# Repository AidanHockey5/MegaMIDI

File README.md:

# Mega MIDI

https://www.aidanlawrence.com/mega-midi-a-playable-version-of-my-hardware-sega-genesis-synth/

[Instruction Manual](https://www.aidanlawrence.com/wp-content/uploads/2019/07/MegaMidi5Manual.pdf)

[Store Link](https://www.aidanlawrence.com/product/mega-midi-5/)

This project contains the source material for the Mega MIDI, a MIDI-controlled Sega Genesis/Megadrive Synthesizer that uses the genuine sound chips from the console itself. The primary FM sound source is the Yamaha YM2612, but I have also included the SN76489 PSG which was also present on the Sega Genesis. This synthesizer does not use emulated sound - it's the real deal. Therefore, you are limited to the limitations of the actual hardware, which I will explain in more detail down below.

# Why Not Just Emulate?
You'd be hard-pressed to find an emulated YM2612 core that sounds exactly like the real YM2612. There are some that get close, but nothing compares to the real thing. Yamaha's FM synthesis is pretty tricky to emulate in the first place, but the YM2612's signature gritty DAC is mostly to blame for the lack of truly accurate emulation. Not with The Mega MIDI though. Since you are using the real YM2612 and SN76489 ICs, you can experience playing the Sega Genesis as a musical instrument with the true fidelity and accuracy as the real thing.

# Play Any Instrument from Any Genesis Video Game Music
The Mega MIDI reads in ".opm" files. OPM files were originally designed for the VOPM virtual synthesizer. The OPM format stores the register data for FM patches that you can use to easily program your YM2612 with. FM synthesis is very complicated, so while you still have the option to create your own FM patches, it would be way easier to just directly take the FM voice patches from the games themselves and use them on your Mega MIDI. With the Mega MIDI, you can, in fact, DIRECTLY play FM patches from any Sega Genesis game's music. These aren't "sound-alike" patches either, they are the actual identical patches lifted directly from the game's source. Do you like ThunderForce's Guitar patch in the track Metal Squad? Play it. Want to try your hand playing Chemical Plant Zone's bass patch? Go for it. Any track. Any instrument. Instantly.

# Where Do I find OPM files?
There are two ways:

1) There is a massive pack of ripped OPM files ready to go that spans almost the entire Genesis library. You can find just about anything in this collection. [Click here to download it.](https://www.aidanlawrence.com/wp-content/uploads/2019/03/2612org-OPMs.zip)
One thing to note: This is a REALLY big collection of files. I don't recommend putting them ALL on your SD card at once as load times will begin to suffer. 

2) You can convert any OPN2(YM2612) .VGM file to an OPM patch using the vgm2opm tool courtesy of [Shiru](https://shiru.untergrund.net) and https://github.com/vampirefrog/fmtools

I have included a windows-compiled binary of vgm2opm within the [tools](https://github.com/AidanHockey5/MegaMIDI/tree/master/tools) directory of this repository along with a batch-file to automatically execute the tool. To use this tool, simply place your desired .vgm/vgz files within the VGM_IN folder, double-click the CONVERT_VGM_OPM.bat file, then retrieve your OPM patch files in the OPM_OUT folder.

# USB MIDI and Traditional DIN MIDI Compatible
Want to control The Mega MIDI through software like Ableton, FL Studio, or any other DAW? You can! The Mega MIDI will show up like any other MIDI-compatible instrument and is able to receive native USB MIDI commands without any sort of serial bridge. 
Prefer old-school traditional 5-pin DIN MIDI instead? Go for it! Bust out that classic MIDI controller and plug it in with zero additional setup required.

# Crystal-Clear Amplification 
Now featuring a modified version of the Mega Amp Mod! Beautifully clear amplification for both the YM3438 and the YM2612!

# 7 "Favorite" Buttons to Quickly Swap Between Your Favorite Patches
While you do have access to every .opm file on your Mega MIDI's SD card, sometimes you'll find the *perfect* patch that you'll want to keep for easy-access later. Simply hold-down one of the seven "favorite" buttons at the bottom of the board and your currently loaded patch will be saved into EEPROM. Because favorite patches are saved to EEPROM, you can access them instantaneously without any load times. Perfect for swapping patches on-the-fly!

# Real Hardware, Real Limitations
Because you are working with the real sound chips, you are also working under their real limitations. The YM2612 is a six-channel sound chip, meaning you can play six individual notes at once. The SN76489 PSG is a 3-channel square-wave-only (excluding noise) chip. In total, you can have nine total channels of sound if you're playing both the PSG and the YM2612 at the same time.

While some might find this a bit limiting, others may enjoy the challenge of getting as much sound as they possibly can within the limits of the genuine hardware. Countless other video game music composers did it, now you can experience it too!

# Open-source
All of my source material has been made open-source. Want to build your own Mega MIDI from scratch? Go for it! Have some modifications in mind? I'd love to see them! If you do decide your own version, please credit me: Aidan Lawrence and refer back to this original repository. Please do not resell this project.

# Tools
The firmware for this project was developed in [Visual Studio Code](https://code.visualstudio.com/) with the [PlatformIO extention.](https://docs.platformio.org/en/latest/ide/vscode.html) I used the Teensyduino (ArduinoTeensy) toolchain.

The schematics/PCB files were made with [KiCAD.](http://kicad.org/) Specifically, version 5.0.2.

Precompiled firmware HEX files can be found here:
https://github.com/AidanHockey5/MegaMIDI/releases/

Here is the schematic:

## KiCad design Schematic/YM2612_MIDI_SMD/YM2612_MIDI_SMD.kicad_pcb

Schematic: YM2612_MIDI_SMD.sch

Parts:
C1, C2, C3, C7, C8, C10, C11, C12, C14, C26, C27, C28: 100nF; C_0805
C4, C5: 22pF; C_0603
C6, C20, C21: 1uF; C_0805
C9, C15, C16, C17, C19, C22, C23, C31, C32, C33: 10uF; C_1206
C13: 220pF; C_0603
C18, C29, C30: 100uF; CP_Elec_6.3x7.7
C24, C25: 270pF; C_0805
D1: 1N4148; D_SOD-123
D2: SS34; D_SMA
D4, D5, D6, D7, D8, D9, D10, D11: LED_Small; LED_0805
DS1: LCD20x04; LCD-20x4
H1, H2, H3, H4, H5: MountingHole; MountingHole_3.2mm_M3
J1: DIN-5_180; din-5
J2: TP_GND; Pin_Header_Straight_1x01_Pitch2.54mm
J3: USB_B
J5: ICSP; Pin_Header_Straight_2x03_Pitch2.54mm
J6: Audio-Jack-3; SWITCHCRAFT_35RAPC4BHN2
J7: Micro_SD_Card; SOFNG_TF_15x15_PUSH_PUSH
L1: 10uH; L_4x4
MP1: GRAPHIC; logo_1
MP2: GRAPHIC; logo_2
MP3: GRAPHIC; logo_3
R1: 10k; R_0805
R2, R6, R10, R11, R12, R13, R14, R15, R16, R17: 220; R_0805
R3: 1k; R_0805
R4, R5: 22; R_0805
R7: 270; R_0805
R8, R30: 51K; R_0805
R9: 2.2k; R_0805
R18, R19: 10K; R_0805
R20, R22: 2.2K; R_0805
R21: 1.3K; R_0805
R23, R26: 6.2K; R_0805
R24, R25: 150K; R_0805
R27, R28: 160K; R_0805
R29: 12K; R_0805
RV1: R_POT; 3362P-1-103LF
SW1: Rotary_Encoder_Switch; RotaryEncoder_Alps_EC11E-Switch_Vertical_H20mm
SW2, SW3, SW4, SW5, SW6, SW7, SW8, SW9, SW10: SW_Push_Dual; SW_TH_Tactile_Omron_B3F-10xx
U1: H11L1; SMDIP-6_W7.62mm
U2: AT90USB1286-AU; TQFP-64_14x14mm_Pitch0.8mm
U3: YM2612; DIP-24_W15.24mm
U4: SN76489; DIP-16_W7.62mm
U5: LM2733XMF; SOT-23-5
U6: LD1117S33TR_SOT223; SOT-223-3_TabPin2
U7: 4050; SOIC-16_3.9x9.9mm_Pitch1.27mm
U8: TL072; SOIC-8_3.9x4.9mm_Pitch1.27mm
U9, U10: LD1117S50TR_SOT223; SOT-223-3_TabPin2
Y1: 16MHz; Crystal_SMD_HC49-SD

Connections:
+2V5: C18.1, R18.2, R19.1, U8.3, U8.5
+3V3: C17.1, C26.1, C28.1, J7.4, U6.2, U7.1
+5V: C1.1, C2.1, C3.1, C7.1, C12.2, C32.2, DS1.2, J5.2, R1.1, R6.1, R7.1, R9.1, RV1.1, U1.6, U2.3 (UVCC), U2.8 (VBUS), U2.21 (VCC), U2.52 (VCC), U2.62 (AREF), U2.64 (AVCC), U3.23 (Vcc), U10.2
+5VA: C11.1, C14.2, C27.1, C31.2, R18.1, U3.22 (AVcc), U4.16 (Vcc), U8.8, U9.2
B1: SW2.1, U2.51 (PA0)
B2: SW4.1, U2.50 (PA1)
B3: SW6.1, U2.49 (PA2)
B4: SW9.1, U2.48 (PA3)
B5: SW3.1, U2.47 (PA4)
B6: SW5.1, U2.46 (PA5)
B7: SW7.1, U2.45 (PA6)
B8: SW10.1, U2.44 (PA7)
D0: DS1.7, U2.61 (PF0), U3.2 (D0), U4.10 (D0)
D1: DS1.8, U2.60 (PF1), U3.3 (D1), U4.11 (D1)
D2: DS1.9, U2.59 (PF2), U3.4 (D2), U4.12 (D2)
D3: DS1.10, U2.58 (PF3), U3.5 (D3), U4.13 (D3)
D4: DS1.11, U2.57 (PF4), U3.6 (D4), U4.15 (D4)
D5: DS1.12, U2.56 (PF5), U3.7 (D5), U4.1 (D5)
D6: DS1.13, U2.55 (PF6), U3.8 (D6), U4.2 (D6)
D7: DS1.14, U2.54 (PF7), U3.9 (D7), U4.3 (D7)
GND: C1.2, C2.2, C3.2, C4.2, C5.2, C6.2, C7.2, C8.2, C9.2, C11.2, C12.1, C14.1, C15.1, C16.1, C17.2, C18.2, C23.1, C26.2, C27.2, C28.2, C31.1, C32.1, C33.2, DS1.1, DS1.5, DS1.16, J3.4, J5.6, J6.3, J7.6, J7.9, R3.2, R10.2, R11.2, R12.2, R13.2, R14.2, R15.2, R16.2, R17.2, R19.2, R20.2, R21.2, R22.2, R29.1, RV1.3, SW1.C, SW1.S2, SW2.4, SW3.4, SW4.4, SW5.4, SW6.4, SW7.4, SW8.4, SW9.4, SW10.4, U1.5, U2.6 (UGND), U2.22 (GND), U2.53 (GND), U2.63 (GND), U3.1 (GND), U3.12 (GND), U3.19 (AGND), U4.6 (OE), U4.8 (GND), U5.2, U6.1, U7.8, U7.9, U7.11, U7.14, U8.4, U9.1, U10.1; also elsewhere on the board
LCD_E: DS1.6, U2.16 (PB6)
LCD_RS: DS1.4, U2.42 (PC7)
LED_1: D4.2, U2.26 (PD1)
LED_2: D5.2, U2.28 (PD3)
LED_3: D6.2, U2.29 (PD4)
LED_4: D7.2, U2.30 (PD5)
LED_5: D8.2, U2.31 (PD6)
LED_6: D9.2, U2.32 (PD7)
LED_7: D10.2, U2.14 (PB4)
LED_8: D11.2, U2.17 (PB7)
L_OUT: C29.2, J6.1
MIDI_IN: R7.2, U1.4, U2.27 (PD2)
MISO: J5.1, J7.7, U2.13 (PB3)
MOL: C19.2, R20.1, U3.21 (MOL)
MOR: C22.2, R22.1, U3.20 (MOR)
MOSI: J5.4, U2.12 (PB2), U7.5
unnamed: C4.1, U2.24 (XTAL1), Y1.2
unnamed: C5.1, U2.23 (XTAL2), Y1.1
unnamed: C6.1, U2.7 (UCAP)
unnamed: C10.2, U3.24 (CLOCK_IN)
unnamed: C13.2, R29.2, R30.2, U5.3
unnamed: C19.1, R23.2
unnamed: C20.1, R24.2
unnamed: C21.1, R25.2
unnamed: C22.1, R26.2
unnamed: C24.1, C29.1, R27.1, U8.1
unnamed: C24.2, R23.1, R24.1, R27.2, U8.2
unnamed: C25.1, C30.1, R28.1, U8.7
unnamed: C25.2, R25.1, R26.1, R28.2, U8.6
unnamed: D1.1, R2.1, U1.1
unnamed: D1.2, J1.5, U1.2
unnamed: D2.2, L1.1, U5.1
unnamed: D4.1, R10.1
unnamed: D5.1, R11.1
unnamed: D6.1, R12.1
unnamed: D7.1, R13.1
unnamed: D8.1, R14.1
unnamed: D9.1, R15.1
unnamed: D10.1, R16.1
unnamed: D11.1, R17.1
unnamed: DS1.3, RV1.2
unnamed: DS1.15, R6.2
unnamed: J1.4, R2.2
unnamed: J7.2, U7.2
unnamed: J7.3, U7.4
unnamed: J7.5, U7.6
unnamed: R3.1, U2.43 (PE2/~HWB)
unnamed: R4.1, U2.5 (D+)
unnamed: R5.1, U2.4 (D-)
unnamed: R8.2, U5.4
PSG_CLOCK: U2.41 (PC6), U4.14 (CLOCK_IN)
PSG_OUT: C20.2, C21.2, R21.1, U4.7 (SN_OUT)
PSG_RDY: R9.2, U2.19 (PE5), U4.4 (READY)
PSG_WE: U2.18 (PE4), U4.5 (WE)
RESET: J5.5, R1.2, SW8.1, U2.20 (~RESET)
RE_A: SW1.A, U2.1 (PE6)
RE_B: SW1.B, U2.2 (PE7)
RE_SW: C8.1, SW1.S1, U2.25 (PD0)
R_OUT: C30.2, J6.2
SCK: J5.3, U2.11 (PB1), U7.7
SD_CS: U2.10 (PB0), U7.3
USB_D+: J3.3, R4.2
USB_D-: J3.2, R5.2
VBOOST: C13.1, C15.2, C16.2, C23.2, C33.1, D2.1, R30.1, U6.3, U9.3, U10.3; also elsewhere on the board
VBUS: C9.1, J3.1, L1.2, R8.1, U5.5
YM_A0: U2.39 (PC4), U3.17 (A0)
YM_A1: U2.40 (PC5), U3.18 (A1)
YM_CLOCK: C10.1, U2.15 (PB5)
YM_CS: U2.36 (PC1), U3.14 (CS)
YM_IC: U2.35 (PC0), U3.11 (IC)
YM_RD: U2.38 (PC3), U3.16 (RD)
YM_WR: U2.37 (PC2), U3.15 (WR)

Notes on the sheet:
YM2612 MIDI Synth SMD Version
Tuesday, Feburary 5, 2019
Designed and Programmed by: Aidan Lawrence www.aidanlawrence.com
MCU
Sound Chips
Mixing, Pre-amp & Power Amp
SD Card & Level Translator
Power Delivery
I/O
LCD
MIDI-In
YM3438 Remove: R20 R22
YM3438 Change: R23, R26 51K

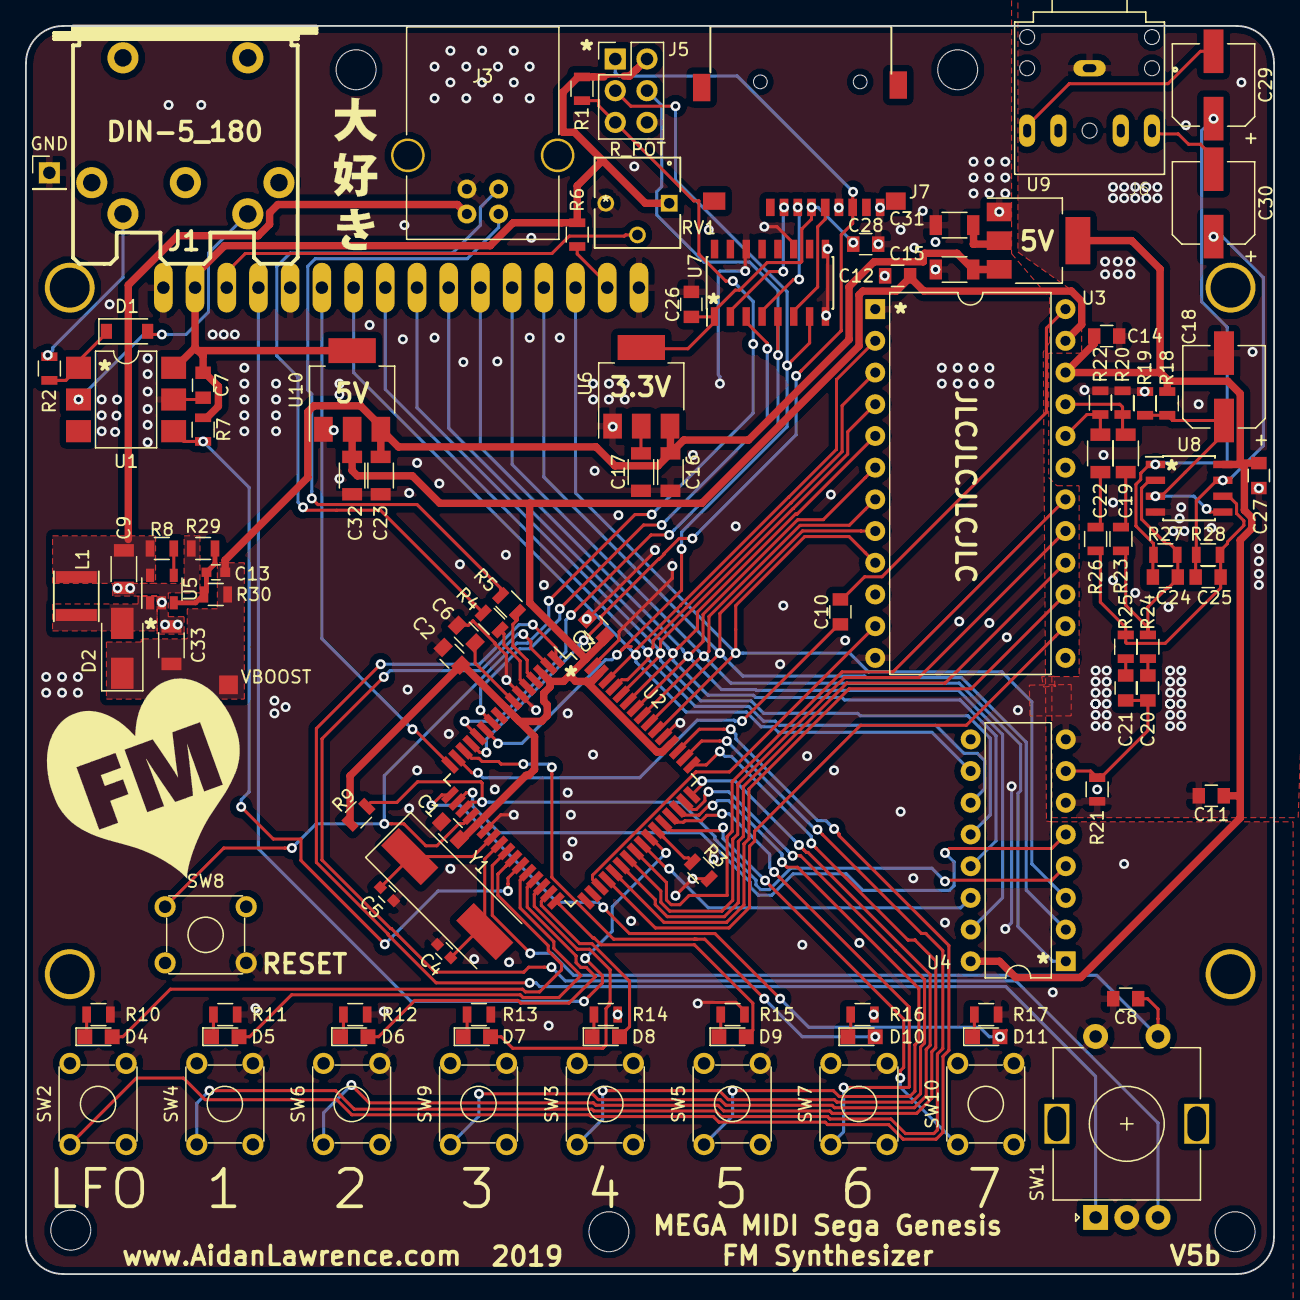
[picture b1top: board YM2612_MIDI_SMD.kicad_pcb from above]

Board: 2 copper layers, 100.0 x 100.0 mm, 112 parts (1 on the bottom side), 93 nets.

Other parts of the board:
GND: TP_GND; Pin_Header_Straight_1x01_Pitch2.54mm
VBOOST: Measurement_Point_Square-SMD-Pad_Small

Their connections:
GND: GND.1; also elsewhere on the board
VBOOST: VBOOST.1; also elsewhere on the board

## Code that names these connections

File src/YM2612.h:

#ifndef YM2612_H_
#define YM2612_H_
#include <Arduino.h>
#include "Adjustments.h"
#include "Voice.h"

#define mask(s) (~(~0<<s))
const int MAX_CHANNELS_YM = 6;

class YM2612
{
private:
    uint8_t _IC = 10;
    uint8_t _CS = 11;
    uint8_t _WR = 12;
    uint8_t _RD = 13;
    uint8_t _A0 = 14;
    uint8_t _A1 = 15;
    typedef struct
    {
        bool keyOn = false;
        uint16_t keyCount = 0;
        bool sustained = false;
        uint8_t keyNumber = 0;
        uint8_t blockNumber = 0;
        uint8_t index = 0;
    } Channel;
    uint8_t lfoFrq = 0;
    uint8_t lfoSens = 7;
    int8_t octaveShift = 0;
    unsigned char bank0[0xB7-0x21]; //Shadow registers
    unsigned char bank1[0xB7-0x30];
    Voice currentVoice;
public:
    YM2612();
    Channel channels[MAX_CHANNELS_YM];
    bool lfoOn = false;
    int8_t GetOctaveShift();
    void SetOctaveShift(int8_t shift);
    void SetChannelOn(uint8_t key, uint8_t velocity, bool velocityEnabled);
    void SetChannelOff(uint8_t key);
    void SetVoice(Voice v);
    float NoteToFrequency(uint8_t note);
    void SetFrequency(uint16_t frequency, uint8_t channel);
    void AdjustLFO(uint8_t value);
    void AdjustPitch(uint8_t channel, int pitch);
    void ReleaseSustainedKeys();
    void ClampSustainedKeys();
    uint16_t CalcFNumber(float note);
    void ShiftOctaveUp();
    void ShiftOctaveDown();
    void ToggleLFO();
    void Reset();
    void send(unsigned char addr, unsigned char data, bool setA1=0);
    void DumpShadowRegisters();
    uint8_t GetShadowValue(uint8_t addr, bool bank);

    //Manual register setting for MIDI exposure
    void SetTL(uint8_t slot, uint8_t op, uint8_t value);
    void SetAR(uint8_t slot, uint8_t op, uint8_t value);
    void SetD1R(uint8_t slot, uint8_t op, uint8_t value);
    void SetD1L(uint8_t slot, uint8_t op, uint8_t value);
    void SetD2R(uint8_t slot, uint8_t op, uint8_t value);
    void SetRR(uint8_t slot, uint8_t op, uint8_t value);
    void SetDetune(uint8_t slot, uint8_t op, uint8_t value);
    void SetMult(uint8_t slot, uint8_t op, uint8_t value);
    void SetRateScaling(uint8_t slot, uint8_t op, uint8_t value);
    void SetAmplitudeModulation(uint8_t slot, uint8_t op, bool value);
    void SetVoiceManual(uint8_t slot, Voice v);
    
    //Globals
    void SetLFOEnabled(bool value);
    void SetLFOFreq(uint8_t value);
    void SetFreqModSens(uint8_t slot, uint8_t value);
    void SetAlgo(uint8_t slot, uint8_t value);
    void SetAMSens(uint8_t slot, uint8_t value);
    void SetFMFeedback(uint8_t slot, uint8_t value);

};
#endif

//Notes
// DIGITAL BUS = PF0-PF7
// IC = PC0/10
// CS = PC1/11
// WR = PC2/12
// RD = PC3/13
// A0 = PC4/14
// A1 = PC5/15

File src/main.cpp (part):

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#define LCD_COLS 20
uint16_t fileNameScrollIndex = 0;
uint8_t lcdSelectionIndex = 0;
LiquidCrystal lcd(17, 26, 38, 39, 40, 41, 42, 43, 44, 45); //PC7 & PB6 + Same data bus as sound chips
bool redrawLCDOnNextLoop = false;
bool stopLCDFileUpdate = false;

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//SD Card
SdFat SD;
File file;
#define SD_CHIP_SELECT SS //PB0 
#define FIRST_FILE 0x00
#define NEXT_FILE 0x01
#define PREV_FILE 0x02
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  //YM2612 and PSG Clock Generation
  pinMode(25, OUTPUT);
  pinMode(16, OUTPUT);
  //8MHz on PB5 (YM2612)
  // set up Timer 1
  TCCR1A = bit (COM1A0);  // toggle OC1A on Compare Match
  TCCR1B = bit (WGM12) | bit (CS10);   // CTC, no prescaling
  OCR1A =  0; //Divide by 2

  //4MHz on PC6 (PSG)
  // set up Timer 3
  TCCR3A = bit (COM3A0);  // toggle OC3A on Compare Match
  TCCR3B = bit (WGM32) | bit (CS30);   // CTC, no prescaling
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
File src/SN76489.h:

#ifndef SN76489_H_
#define SN76489_H_
#include <Arduino.h>
#include "Adjustments.h"

//SN76489 MIDI driver example by: https://github.com/cdodd/teensy-sn76489-midi-synth/blob/master/teensy-sn76489-midi-synth.ino
const int MAX_CHANNELS_PSG = 3;
const int noise = 3;

class SN76489
{
private:
    uint8_t _WE = 36;
    typedef struct
    {
        bool keyOn = false;
        bool sustained = false;
        uint8_t keyNumber = 0;
    } Channel;
    const long clockHz = 4000000;
    const uint8_t attenuationRegister[4] = {0x10, 0x30, 0x50, 0x70};
    const uint8_t frequencyRegister[3] = {0x00, 0x20, 0x40};
    uint8_t currentNote[4] = {0, 0, 0, 0};
    uint8_t currentVelocity[4] = {0, 0, 0, 0};
    int currentPitchBend[3] = {8192, 8192, 8192};
public:
    SN76489();
    Channel channels[MAX_CHANNELS_PSG];
    Channel noiseChannel;
    void SetChannelOn(uint8_t key, uint8_t velocity, bool velocityEnabled);
    void SetChannelOff(uint8_t key);
    void SetNoiseOn(uint8_t key, uint8_t velocity, bool velocityEnabled);
    void MIDISetNoiseControl(byte control, byte value);
    bool UpdateNoiseControl();
    void SetNoiseOff(uint8_t key);
    void ClampSustainedKeys();
    void ReleaseSustainedKeys();
    void UpdateAttenuation(uint8_t voice);
    void SetSquareFrequency(uint8_t voice, int frequencyData);
    bool UpdateSquarePitch(uint8_t voice);
    void PitchChange(uint8_t channel, int pitch);
    void Reset();
    void send(uint8_t data);
};
#endif

//Notes
// DIGITAL BUS = PF0-PF7
// WE = PE4/36
// RDY = PE5/37

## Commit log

2019-01-07 Create F-Number algo, set voice to test piano, send scale to YM
2019-01-09 Full 6 channel polyphony
2019-01-09 Add SD support, parsing opm files. Populate 16 instrument voices with opm data. Not sent to chip yet.
2019-01-09 Users can now select voices from OPM files. Only the single 'test' file works for now
2019-01-10 opm file requests and fixed out-of-bounds opm voice selections
2019-01-10 Added hardware voice swap buttons
2019-01-10 Fixed voice 0 load bug
2019-01-10 Added serial connect tool, added vgm2opm tool
2019-01-10 fixed patch program swapping
2019-01-12 New frequency system and pitch bending
2019-01-12 Clean up old freq. stuff
2019-01-12 Added octave shifting
2019-01-15 Added LFO support
2019-01-15 Added LFO toggle button
2019-01-15 Removed shadow registers
2019-01-15 Little bit of cleanup
2019-01-16 Tuned player to match with known-tuned piano
2019-01-16 Removed LTC6903, replaced with 8MHz crystal. Tuned instrument for 8MHz
2019-01-17 Added basic PSG Support
2019-01-18 Tuned PSG, LFO only responds to control command 0x01 (mod wheel)
2019-01-18 Starting PSG Pitchbend
2019-01-18 Added PSG Pitchbending
2019-01-18 YM2612 driver refactor
2019-01-19 Cleanup and stuff, you know.
2019-01-19 Removed LTC6903 files
2019-01-19 Fixed broken operator registers
2019-01-19 Moved octave shifting for YM to YM driver
2019-01-20 Fixed LFO register reset
2019-01-24 Added hardware MIDI IN
2019-01-25 Fixed pitch bend issue for YM
2019-02-02 Added basic rotary encoder support
2019-02-03 Added some basic LCD routines
2019-02-04 Fixed LCD bug
2019-02-25 schematic rough complete
2019-03-06 Changes for PCB Version
2019-03-07 Added EEPROM Favorite Get/Put
2019-03-07 Added SD failure mode
2019-03-08 LCD shows favorites & fixed YM pitchbend
2019-03-08 Fixed unresponsive favorite 7 button
2019-03-08 Removed old debug printout
2019-04-10 Starting fix on PSG noise channel
2019-04-14 Fixed opm parser bug
2019-04-17 Fixed upper bank voice bug and added YM shadow registers + readout
2019-04-17 New YM Octave shift option on LCD. Saves to EEPROM favorites
2019-04-22 Added YM sustain pedal support
2019-04-22 Finished PSG and YM sustain pedal support
2019-04-22 Cleanup
2019-04-23 Adjusted USB device name
2019-04-23 tools folders
2019-04-23 Added schematic files
2019-04-23 Added schematic libs
2019-04-26 new ibom
2019-04-26 Added library cache
2019-04-26 Added footprint cache
2019-04-28 Added tool EXEs and fixed serial
2019-04-28 Fixed PSG sustain
2019-04-28 V1.0 firmware complete
2019-04-28 Added center-positive logo to FSS
2019-04-30 Added YM key velocity setting on MIDI CHANNEL 3
2019-04-30 YM and PSG now both have optional velocity. Added ArduinoISP scripts and tools
2019-05-02 YM key-rollover
2019-05-03 Velocity is iffy on a 6-voice synth. No velocity now made default MIDI CH 1-2
2019-05-05 Check for files with 'no voices'
2019-05-06 Added alternative build options
2019-05-06 Updated flasher script with teensy dir wildcard
2019-05-12 Changed build options
2019-05-16 Fixed minor bug on favorite button #7
2019-05-20 Move cursor off of file browser line to prevent LCD from updating, causing noise
2019-05-27 Tiny cleanup
2019-06-01 Moved LCD redraw out of rotary encoder interrupt
2019-06-14 LC filter value correction
2019-06-23 Begin hardware revision. New amp
2019-06-23 Re-annotate
2019-06-29 New power delivery
2019-06-29 Pre-reroute
2019-06-30 Analog stage
2019-06-30 Route complete
2019-06-30 Silk screen
2019-07-01 PCB Complete
2019-07-05 Amend PSG resistors
2019-07-05 Adjusted resistor values
2019-07-10 New boost circuit
2019-07-16 Amplifier notations
2019-07-17 Update flash script. Keydown now stops LCD filename from updating
2019-07-28 PSG Noise support on MIDI CH. 5
2019-08-05 New meta folder removal. No more MacOS garbage files!
2019-09-10 Beginning work on new VST control. Tweak those synth parms!
2019-09-11 framework laid out. Needs to be verified and cleaned
2019-09-11 Working on keyon-keyoff
2019-09-14 Remove map commands for FM patches
2019-09-16 VST Patch syncing complete
2019-09-16 Added flasher usb drivers
2019-09-17 New patch programming via SysEx
2019-09-17 Trying to strike a balance between VST functionality and old version ease of use
2019-09-19 New MIDI channel scheme
2019-09-21 Per-slot patch setting. Fixed key-off algo for individual slots
2019-11-14 Moved to monotimbral design
2019-11-14 Old key on/off algo
2019-11-16 VST favorites and VST LCD indicator
2019-11-18 New flashing script
2019-11-18 linux support on flasher script
2019-11-19 Fixed macos upload
2019-11-19 Linux support for flasher
2019-11-19 Flasher script now runs at 19200 baud
2019-11-19 Updated Flasher text
2019-11-19 Create windows binary script
2019-11-20 import Queue
2019-11-20 Macos SSL fix
2019-11-21 Changed url comments in flasher script
2019-11-22 Use Nuitka for macos flasher
2019-11-22 Nvm back to cxfreeze
2019-11-22 SSL for macos
2019-11-22 Remove dummy files
2019-11-23 Flasher readme
2021-02-16 Operator order fix
2021-02-16 Add LFO toggle to voice-set
2021-05-27 Filename scrolling reset fix
2021-05-27 fix: couldn't access last (64th) voice in opm file
2021-05-27 Increment version number
2021-11-09 Update README.md
    https://forum.kicad.info/t/warning-avoid-all-links-to-kicad-pcb-org-use-kicad-org/31521
2022-04-03 Encoder invert option

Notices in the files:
parts and their libraries:
Copyright 2016 Accelerated Designs. All rights reserved.
